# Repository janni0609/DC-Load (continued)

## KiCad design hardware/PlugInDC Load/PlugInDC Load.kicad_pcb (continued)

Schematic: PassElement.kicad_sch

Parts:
C1: 100n; C_0603_1608Metric; not fitted
C2: 10n; C_0603_1608Metric
C3: 100n; C_0603_1608Metric
D1, D2: 1N4148WX; D_SOD-323
F1: 10A; Fuse_1206_3216Metric
H1, H2: M3; MountingHole_3.2mm_M3_DIN965_Pad
Q1: MJH6284; MR30
R2, R3, R4, R10, R11: 1k; R_0603_1608Metric
R5: 500; R_0603_1608Metric; not fitted
R6: 10k; R_0603_1608Metric
R7, R9: 62k; R_0603_1608Metric
R8: 150; R_1206_3216Metric
R12: 0,005; R_2512_6332Metric
TP1: Int-; TestPoint_Pad_D1.0mm
TP2: CurrO; TestPoint_Pad_D1.0mm
TP3: IntO; TestPoint_Pad_D1.0mm
TP4: B; TestPoint_Pad_D1.0mm
TP5: CrrH; TestPoint_Pad_D1.0mm
TP6: CurrL; TestPoint_Pad_D1.0mm
U3: TLV9152; SOT-23-8

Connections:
+5V: C3.2, U3.8 (V+); also elsewhere on the board
/PassElementsAll/Imeas: R4.1; also elsewhere on the board
/PassElementsAll/Iset: R2.1; also elsewhere on the board
/PassElementsAll/ON/OFF: D2.1 (K); also elsewhere on the board
/PassElementsAll/PassElement2/Emitter: F1.1, Q1.3 (E)
/PassElementsAll/PassElement2/R_to_F: F1.2, R10.2, R12.1, TP5.1 (1_1)
/PassElementsAll/unreg_mon: D1.1 (K); also elsewhere on the board
GND: C3.1, R6.1, R9.2, U3.4 (V-); also elsewhere on the board
GNDPWR: H1.1 (1_1), R11.2, R12.2, TP6.1 (1_1); also elsewhere on the board
unnamed: C1.2, R5.1
unnamed: C2.2, D1.2 (A), R5.2, R6.2, R8.1, TP3.1 (1_1), U3.1
unnamed: D2.2 (A), Q1.1 (B), R8.2, TP4.1 (1_1)
unnamed: R3.2, R4.2, R7.1, TP2.1 (1_1), U3.7
unnamed: R2.2, U3.3 (+)
unnamed: C1.1, C2.1, R3.1, TP1.1 (1_1), U3.2 (-)
unnamed: R9.1, R10.1, U3.5 (+)
unnamed: R7.2, R11.1, U3.6 (-)
VBUS: H2.1 (1_1), Q1.2 (C); also elsewhere on the board

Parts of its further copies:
C23, C26, C29, C32, C35, C38, C41, C44, C47, C50, C53, C56, C59: 100n; C_0603_1608Metric; not fitted
C24, C27, C30, C33, C36, C39, C42, C45, C48, C51, C54, C57, C60: 10n; C_0603_1608Metric
C25, C28, C31, C34, C37, C40, C43, C46, C49, C52, C55, C58, C61: 100n; C_0603_1608Metric
D15, D16, D17, D18, D19, D20, D21, D22, D23, D24, D25, D26, D27, D28, D29, D30, D31, D32, D33, D34, D35, D36, D37, D38, D39, D40: 1N4148WX; D_SOD-323
F4, F5, F6, F7, F8, F9, F10, F11, F12, F13, F14, F15, F16: 10A; Fuse_1206_3216Metric
H5, H6, H7, H8, H9, H10, H11, H12, H13, H14, H15, H16, H17, H18, H19, H20, H21, H22, H23, H24, H25, H26, H27, H28, H29, H30: M3; MountingHole_3.2mm_M3_DIN965_Pad
Q3, Q4, Q5, Q6, Q7, Q8, Q9, Q10, Q11, Q12, Q13, Q14, Q15: MJH6284; MR30
R23, R24, R25, R31, R32, R34, R35, R36, R42, R43, R45, R46, R47, R53, R54, R56, R57, R58, R64, R65, R67, R68, R69, R75, R76, R78, R79, R80, R86, R87, R89, R90, R91, R97, R98, R100, R101, R102, R108, R109, R111, R112, R113, R119, R120, R122, R123, R124, R130, R131, R133, R134, R135, R141, R142, R144, R145, R146, R152, R153, R155, R156, R157, R163, R164: 1k; R_0603_1608Metric
R26, R37, R48, R59, R70, R81, R92, R103, R114, R125, R136, R147, R158: 500; R_0603_1608Metric; not fitted
R27, R38, R49, R60, R71, R82, R93, R104, R115, R126, R137, R148, R159: 10k; R_0603_1608Metric
R28, R30, R39, R41, R50, R52, R61, R63, R72, R74, R83, R85, R94, R96, R105, R107, R116, R118, R127, R129, R138, R140, R149, R151, R160, R162: 62k; R_0603_1608Metric
R29, R40, R51, R62, R73, R84, R95, R106, R117, R128, R139, R150, R161: 150; R_1206_3216Metric
R33, R44, R55, R66, R77, R88, R99, R110, R121, R132, R143, R154, R165: 0,005; R_2512_6332Metric
TP7, TP13, TP19, TP25, TP31, TP37, TP43, TP49, TP55, TP61, TP67, TP73, TP79: Int-; TestPoint_Pad_D1.0mm
TP8, TP14, TP20, TP26, TP32, TP38, TP44, TP50, TP56, TP62, TP68, TP74, TP80: CurrO; TestPoint_Pad_D1.0mm
TP9, TP15, TP21, TP27, TP33, TP39, TP45, TP51, TP57, TP63, TP69, TP75, TP81: IntO; TestPoint_Pad_D1.0mm
TP10, TP16, TP22, TP28, TP34, TP40, TP46, TP52, TP58, TP64, TP70, TP76, TP82: B; TestPoint_Pad_D1.0mm
TP11, TP17, TP23, TP29, TP35, TP41, TP47, TP53, TP59, TP65, TP71, TP77, TP83: CrrH; TestPoint_Pad_D1.0mm
TP12, TP18, TP24, TP30, TP36, TP42, TP48, TP54, TP60, TP66, TP72, TP78, TP84: CurrL; TestPoint_Pad_D1.0mm
U8, U9, U10, U11, U12, U13, U14, U15, U16, U17, U18, U19, U20: TLV9152; SOT-23-8

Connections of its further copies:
+5V: C25.2, C28.2, C31.2, C34.2, C37.2, C40.2, C43.2, C46.2, C49.2, C52.2, C55.2, C58.2, C61.2, U8.8 (V+), U9.8 (V+), U10.8 (V+), U11.8 (V+), U12.8 (V+), U13.8 (V+), U14.8 (V+), U15.8 (V+), U16.8 (V+), U17.8 (V+), U18.8 (V+), U19.8 (V+), U20.8 (V+); also elsewhere on the board
/PassElementsAll/Imeas: R25.1, R36.1, R47.1, R58.1, R69.1, R80.1, R91.1, R102.1, R113.1, R124.1, R135.1, R146.1, R157.1; also elsewhere on the board
/PassElementsAll/Iset: R23.1, R34.1, R45.1, R56.1, R67.1, R78.1, R89.1, R100.1, R111.1, R122.1, R133.1, R144.1, R155.1; also elsewhere on the board
/PassElementsAll/ON/OFF: D16.1 (K), D18.1 (K), D20.1 (K), D22.1 (K), D24.1 (K), D26.1 (K), D28.1 (K), D30.1 (K), D32.1 (K), D34.1 (K), D36.1 (K), D38.1 (K), D40.1 (K); also elsewhere on the board
/PassElementsAll/PassElement1/Emitter: F4.1, Q3.3 (E)
/PassElementsAll/PassElement1/R_to_F: F4.2, R31.2, R33.1, TP11.1 (1_1)
/PassElementsAll/PassElement3/Emitter: F5.1, Q4.3 (E)
/PassElementsAll/PassElement3/R_to_F: F5.2, R42.2, R44.1, TP17.1 (1_1)
/PassElementsAll/PassElement4/Emitter: F6.1, Q5.3 (E)
/PassElementsAll/PassElement4/R_to_F: F6.2, R53.2, R55.1, TP23.1 (1_1)
/PassElementsAll/PassElement5/Emitter: F7.1, Q6.3 (E)
/PassElementsAll/PassElement5/R_to_F: F7.2, R64.2, R66.1, TP29.1 (1_1)
/PassElementsAll/PassElement6/Emitter: F8.1, Q7.3 (E)
/PassElementsAll/PassElement6/R_to_F: F8.2, R75.2, R77.1, TP35.1 (1_1)
/PassElementsAll/PassElement7/Emitter: F9.1, Q8.3 (E)
/PassElementsAll/PassElement7/R_to_F: F9.2, R86.2, R88.1, TP41.1 (1_1)
/PassElementsAll/PassElement8/Emitter: F10.1, Q9.3 (E)
/PassElementsAll/PassElement8/R_to_F: F10.2, R97.2, R99.1, TP47.1 (1_1)
/PassElementsAll/PassElement9/Emitter: F11.1, Q10.3 (E)
/PassElementsAll/PassElement9/R_to_F: F11.2, R108.2, R110.1, TP53.1 (1_1)
/PassElementsAll/PassElement10/Emitter: F12.1, Q11.3 (E)
/PassElementsAll/PassElement10/R_to_F: F12.2, R119.2, R121.1, TP59.1 (1_1)
/PassElementsAll/PassElement11/Emitter: F13.1, Q12.3 (E)
/PassElementsAll/PassElement11/R_to_F: F13.2, R130.2, R132.1, TP65.1 (1_1)
/PassElementsAll/PassElement12/Emitter: F14.1, Q13.3 (E)
/PassElementsAll/PassElement12/R_to_F: F14.2, R141.2, R143.1, TP71.1 (1_1)
/PassElementsAll/PassElement13/Emitter: F16.1, Q15.3 (E)
/PassElementsAll/PassElement13/R_to_F: F16.2, R163.2, R165.1, TP83.1 (1_1)
/PassElementsAll/PassElement14/Emitter: F15.1, Q14.3 (E)
/PassElementsAll/PassElement14/R_to_F: F15.2, R152.2, R154.1, TP77.1 (1_1)
/PassElementsAll/unreg_mon: D15.1 (K), D17.1 (K), D19.1 (K), D21.1 (K), D23.1 (K), D25.1 (K), D27.1 (K), D29.1 (K), D31.1 (K), D33.1 (K), D35.1 (K), D37.1 (K), D39.1 (K); also elsewhere on the board
GND: C25.1, C28.1, C31.1, C34.1, C37.1, C40.1, C43.1, C46.1, C49.1, C52.1, C55.1, C58.1, C61.1, R27.1, R30.2, R38.1, R41.2, R49.1, R52.2, R60.1, R63.2, R71.1, R74.2, R82.1, R85.2, R93.1, R96.2, R104.1, R107.2, R115.1, R118.2, R126.1, R129.2, R137.1, R140.2, R148.1, R151.2, R159.1, R162.2, U8.4 (V-), U9.4 (V-), U10.4 (V-), U11.4 (V-), U12.4 (V-), U13.4 (V-), U14.4 (V-), U15.4 (V-), U16.4 (V-), U17.4 (V-), U18.4 (V-), U19.4 (V-), U20.4 (V-); also elsewhere on the board
GNDPWR: H5.1 (1_1), H7.1 (1_1), H9.1 (1_1), H11.1 (1_1), H13.1 (1_1), H15.1 (1_1), H17.1 (1_1), H19.1 (1_1), H21.1 (1_1), H23.1 (1_1), H25.1 (1_1), H27.1 (1_1), H29.1 (1_1), R32.2, R33.2, R43.2, R44.2, R54.2, R55.2, R65.2, R66.2, R76.2, R77.2, R87.2, R88.2, R98.2, R99.2, R109.2, R110.2, R120.2, R121.2, R131.2, R132.2, R142.2, R143.2, R153.2, R154.2, R164.2, R165.2, TP12.1 (1_1), TP18.1 (1_1), TP24.1 (1_1), TP30.1 (1_1), TP36.1 (1_1), TP42.1 (1_1), TP48.1 (1_1), TP54.1 (1_1), TP60.1 (1_1), TP66.1 (1_1), TP72.1 (1_1), TP78.1 (1_1), TP84.1 (1_1); also elsewhere on the board
unnamed: C23.2, R26.1
unnamed: C26.2, R37.1
unnamed: C29.2, R48.1
unnamed: C32.2, R59.1
unnamed: C35.2, R70.1
unnamed: C38.2, R81.1
unnamed: C41.2, R92.1
unnamed: C44.2, R103.1
unnamed: C47.2, R114.1
unnamed: C50.2, R125.1
unnamed: C53.2, R136.1
unnamed: C56.2, R147.1
unnamed: C59.2, R158.1
unnamed: C24.2, D15.2 (A), R26.2, R27.2, R29.1, TP9.1 (1_1), U8.1
unnamed: D16.2 (A), Q3.1 (B), R29.2, TP10.1 (1_1)
unnamed: C27.2, D17.2 (A), R37.2, R38.2, R40.1, TP15.1 (1_1), U9.1
unnamed: D18.2 (A), Q4.1 (B), R40.2, TP16.1 (1_1)
unnamed: C30.2, D19.2 (A), R48.2, R49.2, R51.1, TP21.1 (1_1), U10.1
unnamed: D20.2 (A), Q5.1 (B), R51.2, TP22.1 (1_1)
unnamed: C33.2, D21.2 (A), R59.2, R60.2, R62.1, TP27.1 (1_1), U11.1
unnamed: D22.2 (A), Q6.1 (B), R62.2, TP28.1 (1_1)
unnamed: C36.2, D23.2 (A), R70.2, R71.2, R73.1, TP33.1 (1_1), U12.1
unnamed: D24.2 (A), Q7.1 (B), R73.2, TP34.1 (1_1)
unnamed: C39.2, D25.2 (A), R81.2, R82.2, R84.1, TP39.1 (1_1), U13.1
unnamed: D26.2 (A), Q8.1 (B), R84.2, TP40.1 (1_1)
unnamed: C42.2, D27.2 (A), R92.2, R93.2, R95.1, TP45.1 (1_1), U14.1
unnamed: D28.2 (A), Q9.1 (B), R95.2, TP46.1 (1_1)
unnamed: C45.2, D29.2 (A), R103.2, R104.2, R106.1, TP51.1 (1_1), U15.1
unnamed: D30.2 (A), Q10.1 (B), R106.2, TP52.1 (1_1)
unnamed: C48.2, D31.2 (A), R114.2, R115.2, R117.1, TP57.1 (1_1), U16.1
unnamed: D32.2 (A), Q11.1 (B), R117.2, TP58.1 (1_1)
unnamed: C51.2, D33.2 (A), R125.2, R126.2, R128.1, TP63.1 (1_1), U17.1
unnamed: D34.2 (A), Q12.1 (B), R128.2, TP64.1 (1_1)
unnamed: C54.2, D35.2 (A), R136.2, R137.2, R139.1, TP69.1 (1_1), U18.1
unnamed: D36.2 (A), Q13.1 (B), R139.2, TP70.1 (1_1)
unnamed: C57.2, D37.2 (A), R147.2, R148.2, R150.1, TP75.1 (1_1), U19.1
unnamed: D38.2 (A), Q14.1 (B), R150.2, TP76.1 (1_1)
unnamed: C60.2, D39.2 (A), R158.2, R159.2, R161.1, TP81.1 (1_1), U20.1
unnamed: D40.2 (A), Q15.1 (B), R161.2, TP82.1 (1_1)
unnamed: R24.2, R25.2, R28.1, TP8.1 (1_1), U8.7
unnamed: R35.2, R36.2, R39.1, TP14.1 (1_1), U9.7
unnamed: R46.2, R47.2, R50.1, TP20.1 (1_1), U10.7
unnamed: R57.2, R58.2, R61.1, TP26.1 (1_1), U11.7
unnamed: R68.2, R69.2, R72.1, TP32.1 (1_1), U12.7
unnamed: R79.2, R80.2, R83.1, TP38.1 (1_1), U13.7
unnamed: R90.2, R91.2, R94.1, TP44.1 (1_1), U14.7
unnamed: R101.2, R102.2, R105.1, TP50.1 (1_1), U15.7
unnamed: R112.2, R113.2, R116.1, TP56.1 (1_1), U16.7
unnamed: R123.2, R124.2, R127.1, TP62.1 (1_1), U17.7
unnamed: R134.2, R135.2, R138.1, TP68.1 (1_1), U18.7
unnamed: R145.2, R146.2, R149.1, TP74.1 (1_1), U19.7
unnamed: R156.2, R157.2, R160.1, TP80.1 (1_1), U20.7
unnamed: R23.2, U8.3 (+)
unnamed: C23.1, C24.1, R24.1, TP7.1 (1_1), U8.2 (-)
unnamed: R30.1, R31.1, U8.5 (+)
unnamed: R28.2, R32.1, U8.6 (-)
unnamed: R34.2, U9.3 (+)
unnamed: C26.1, C27.1, R35.1, TP13.1 (1_1), U9.2 (-)
unnamed: R41.1, R42.1, U9.5 (+)
unnamed: R39.2, R43.1, U9.6 (-)
unnamed: R45.2, U10.3 (+)
unnamed: C29.1, C30.1, R46.1, TP19.1 (1_1), U10.2 (-)
unnamed: R52.1, R53.1, U10.5 (+)
unnamed: R50.2, R54.1, U10.6 (-)
unnamed: R56.2, U11.3 (+)
unnamed: C32.1, C33.1, R57.1, TP25.1 (1_1), U11.2 (-)
unnamed: R63.1, R64.1, U11.5 (+)
unnamed: R61.2, R65.1, U11.6 (-)
unnamed: R67.2, U12.3 (+)
unnamed: C35.1, C36.1, R68.1, TP31.1 (1_1), U12.2 (-)
unnamed: R74.1, R75.1, U12.5 (+)
unnamed: R72.2, R76.1, U12.6 (-)
unnamed: R78.2, U13.3 (+)
unnamed: C38.1, C39.1, R79.1, TP37.1 (1_1), U13.2 (-)
unnamed: R85.1, R86.1, U13.5 (+)
unnamed: R83.2, R87.1, U13.6 (-)
unnamed: R89.2, U14.3 (+)
unnamed: C41.1, C42.1, R90.1, TP43.1 (1_1), U14.2 (-)
unnamed: R96.1, R97.1, U14.5 (+)
unnamed: R94.2, R98.1, U14.6 (-)
unnamed: R100.2, U15.3 (+)
unnamed: C44.1, C45.1, R101.1, TP49.1 (1_1), U15.2 (-)
unnamed: R107.1, R108.1, U15.5 (+)
unnamed: R105.2, R109.1, U15.6 (-)
unnamed: R111.2, U16.3 (+)
unnamed: C47.1, C48.1, R112.1, TP55.1 (1_1), U16.2 (-)
unnamed: R118.1, R119.1, U16.5 (+)
unnamed: R116.2, R120.1, U16.6 (-)
unnamed: R122.2, U17.3 (+)
unnamed: C50.1, C51.1, R123.1, TP61.1 (1_1), U17.2 (-)
unnamed: R129.1, R130.1, U17.5 (+)
unnamed: R127.2, R131.1, U17.6 (-)
unnamed: R133.2, U18.3 (+)
unnamed: C53.1, C54.1, R134.1, TP67.1 (1_1), U18.2 (-)
unnamed: R140.1, R141.1, U18.5 (+)
unnamed: R138.2, R142.1, U18.6 (-)
unnamed: R144.2, U19.3 (+)
unnamed: C56.1, C57.1, R145.1, TP73.1 (1_1), U19.2 (-)
unnamed: R151.1, R152.1, U19.5 (+)
unnamed: R149.2, R153.1, U19.6 (-)
unnamed: R155.2, U20.3 (+)
unnamed: C59.1, C60.1, R156.1, TP79.1 (1_1), U20.2 (-)
unnamed: R162.1, R163.1, U20.5 (+)
unnamed: R160.2, R164.1, U20.6 (-)
VBUS: H6.1 (1_1), H8.1 (1_1), H10.1 (1_1), H12.1 (1_1), H14.1 (1_1), H16.1 (1_1), H18.1 (1_1), H20.1 (1_1), H22.1 (1_1), H24.1 (1_1), H26.1 (1_1), H28.1 (1_1), H30.1 (1_1), Q3.2 (C), Q4.2 (C), Q5.2 (C), Q6.2 (C), Q7.2 (C), Q8.2 (C), Q9.2 (C), Q10.2 (C), Q11.2 (C), Q12.2 (C), Q13.2 (C), Q14.2 (C), Q15.2 (C); also elsewhere on the board

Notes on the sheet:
Supply: max 5V ~25mA
0 - 2,5V 0 - 8,0645A
2,5V
G = 62

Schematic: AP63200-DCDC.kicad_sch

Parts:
C14: 10u; C_1206_3216Metric
C15, C16, C22: 100n; C_0603_1608Metric
C17: 100p; C_0603_1608Metric
C18, C19, C20, C21: 10u; C_0805_2012Metric
L1: 10u; L_APV_ANR8040
R21: 150k; R_0603_1608Metric
R22: 20k; R_0603_1608Metric
U7: AP63200WU; TSOT-23-6

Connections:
+12V: C14.1, C15.1, U7.2 (EN), U7.3 (IN); also elsewhere on the board
/Power Supply/AP63200-DCDC/SW: C16.2, L1.1, U7.5 (SW)
/Power Supply/AP63200-DCDC/Vout: C17.1, C18.1, C19.1, C20.1, C21.1, C22.1, L1.2, R21.1; also elsewhere on the board
GND: C14.2, C15.2, C18.2, C19.2, C20.2, C21.2, C22.2, R22.2, U7.4 (GND); also elsewhere on the board
unnamed: C16.1, U7.6 (BST)
unnamed: C17.2, R21.2, R22.1, U7.1 (FB)

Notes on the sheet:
6,8V

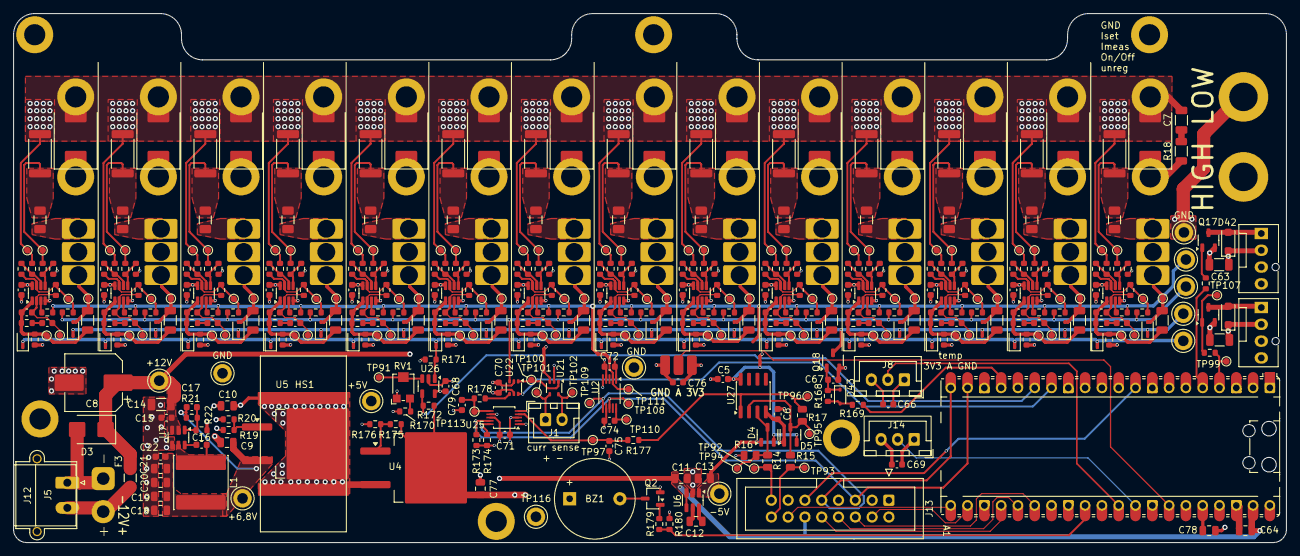
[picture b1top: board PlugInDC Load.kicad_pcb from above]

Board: 4 copper layers, 192.5 x 80.0 mm, 525 parts (0 on the bottom side), 201 nets.

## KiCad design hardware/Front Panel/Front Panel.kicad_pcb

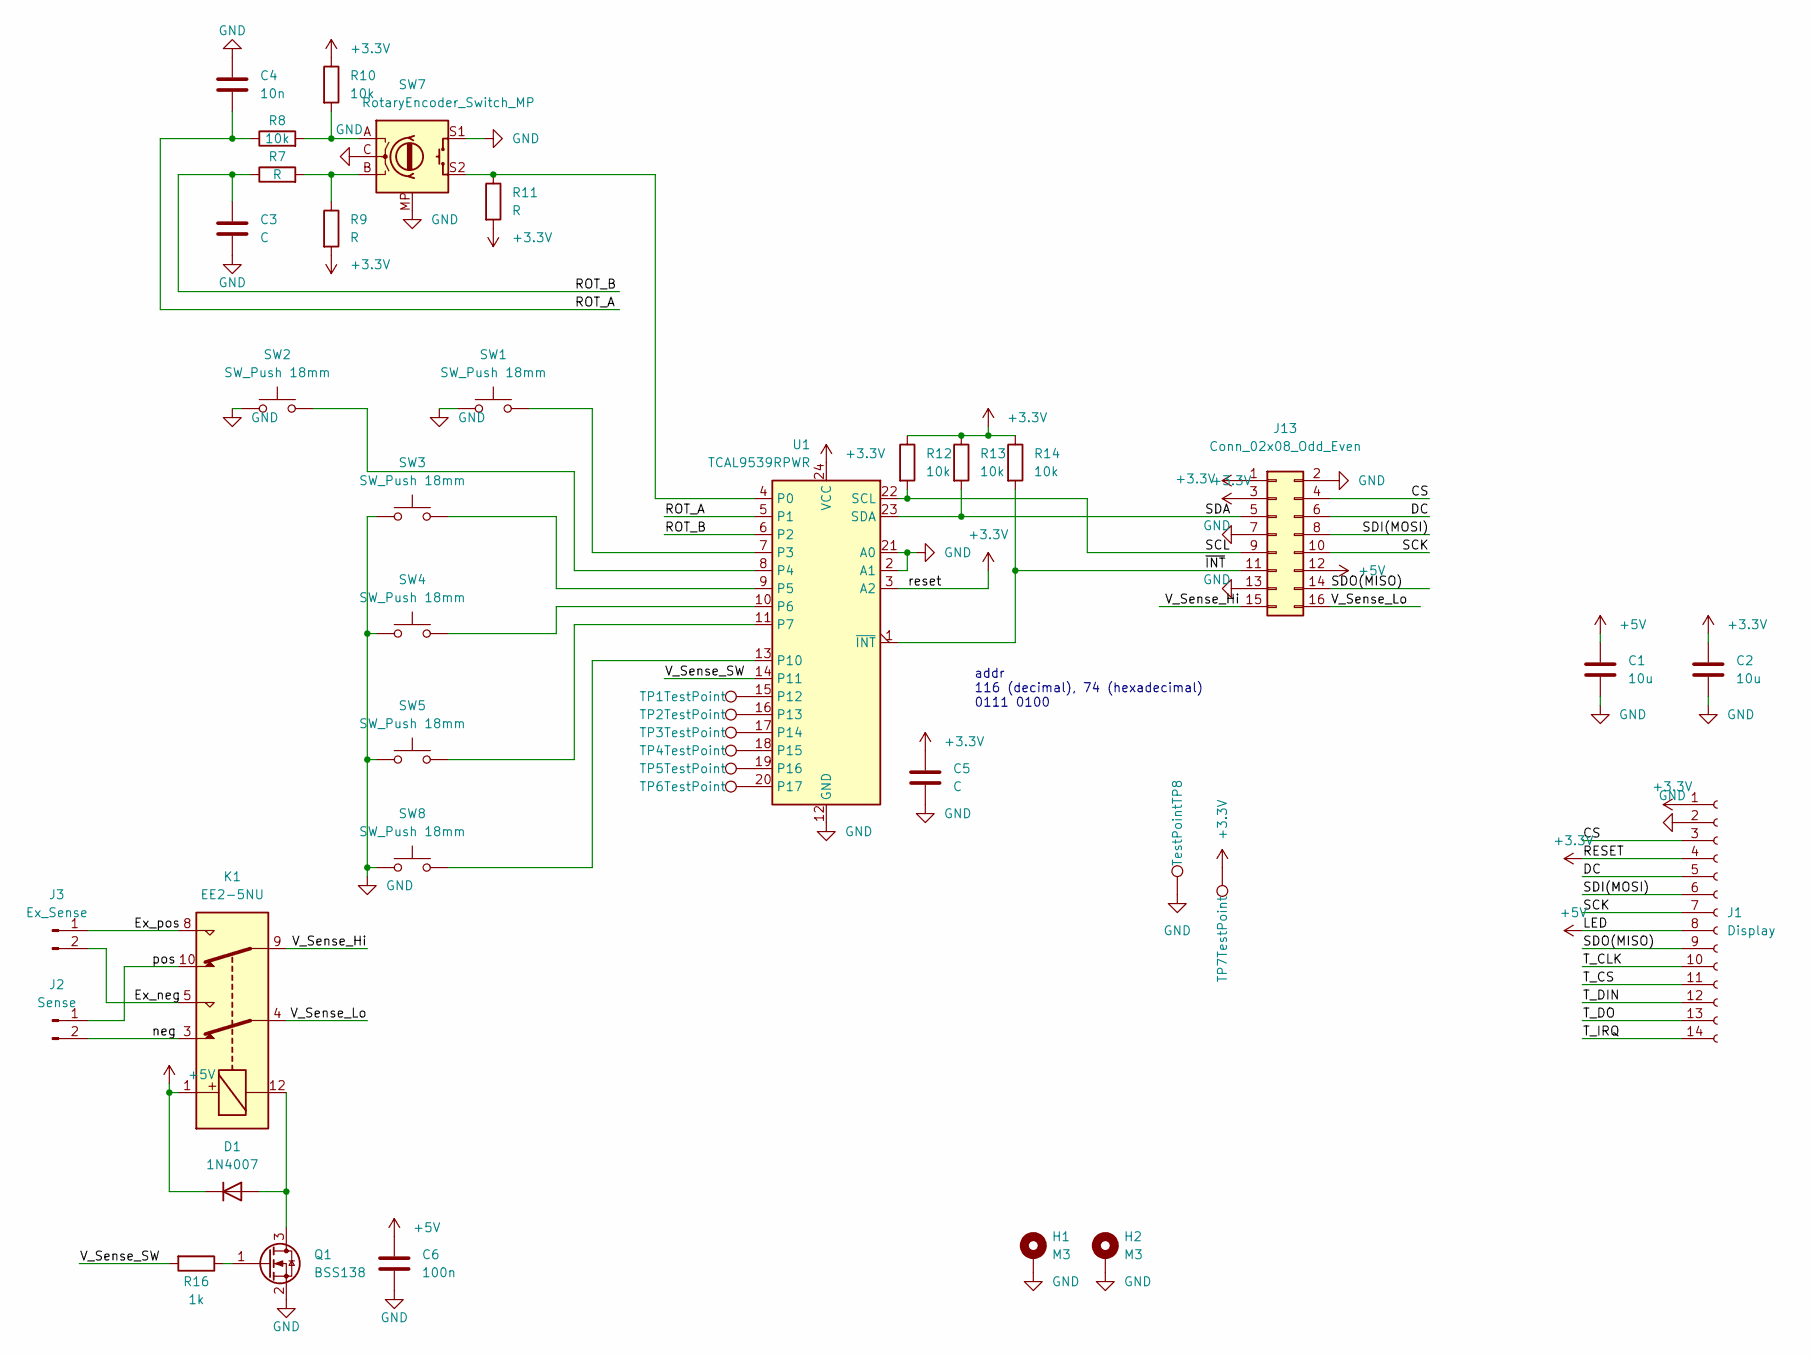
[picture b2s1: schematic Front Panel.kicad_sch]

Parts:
C1, C2: 10u
C3, C5: C
C4: 10n
C6: 100n
D1: 1N4007; D_SOD-123F
H1, H2: M3
J1: Display
J2: Sense
J3: Ex_Sense
J13: Conn_02x08_Odd_Even
K1: EE2-5NU; Relay_DPDT_Kemet_EE2_NU
Q1: BSS138; SOT-23
R7, R9, R11: R
R8, R10, R12, R13, R14: 10k
R16: 1k
SW1, SW2, SW3, SW4, SW5, SW8: SW_Push 18mm
SW7: RotaryEncoder_Switch_MP
TP1, TP2, TP3, TP4, TP5, TP6: TestPoint; TestPoint_Pad_D1.0mm
TP7, TP8: TestPoint; TestPoint_Pad_D1.5mm
U1: TCAL9539RPWR; TSSOP-24_4.4x7.8mm_P0.65mm

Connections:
+3.3V: C2.1, C5.1, J1.1, J1.4, J13.1, J13.3, R9.2, R10.1, R11.2, R12.1, R13.1, R14.1, TP7.1 (1_1), U1.3 (A2), U1.24 (VCC)
+5V: C1.1, C6.1, D1.1 (K), J1.8, J13.12, K1.1
/CS: J1.3, J13.4
/DC: J1.5, J13.6
/Ex_neg: J3.2, K1.5
/Ex_pos: J3.1, K1.8
/ROT_A: C4.1, R8.1, U1.5 (P1)
/ROT_B: C3.1, R7.1, U1.6 (P2)
/SCK: J1.7, J13.10
/SCL: J13.9, R12.2, U1.22 (SCL)
/SDA: J13.5, R13.2, U1.23 (SDA)
/SDI(MOSI): J1.6, J13.8
/SDO(MISO): J1.9, J13.14
/T_CLK: J1.10
/T_CS: J1.11
/T_DIN: J1.12
/T_DO: J1.13
/T_IRQ: J1.14
/V_Sense_Hi: J13.15, K1.9
/V_Sense_Lo: J13.16, K1.4
/V_Sense_SW: R16.2, U1.14 (P11)
/neg: J2.2, K1.3
/pos: J2.1, K1.10
/~INT: J13.11, R14.2, U1.1 (~INT)
GND: C1.2, C2.2, C3.2, C4.2, C5.2, C6.2, H1.1 (1_1), H2.1 (1_1), J1.2, J13.2, J13.7, J13.13, Q1.2 (S), SW1.1, SW2.1, SW3.1, SW4.1, SW5.1, SW7.C, SW7.MP, SW7.S1, SW8.1, TP8.1 (1_1), U1.2 (A1), U1.12 (GND), U1.21 (A0)
unnamed: D1.2 (A), K1.12, Q1.3 (D)
unnamed: Q1.1 (G), R16.1
unnamed: R7.2, R9.1, SW7.B
unnamed: R8.2, R10.2, SW7.A
unnamed: R11.1, SW7.S2, U1.4 (P0)
unnamed: SW1.2, U1.7 (P3)
unnamed: SW2.2, U1.8 (P4)
unnamed: SW3.2, U1.9 (P5)
unnamed: SW4.2, U1.10 (P6)
unnamed: SW5.2, U1.11 (P7)
unnamed: SW8.2, U1.13 (P10)
unnamed: TP1.1 (1_1), U1.15 (P12)
unnamed: TP2.1 (1_1), U1.16 (P13)
unnamed: TP3.1 (1_1), U1.17 (P14)
unnamed: TP4.1 (1_1), U1.18 (P15)
unnamed: TP5.1 (1_1), U1.19 (P16)
unnamed: TP6.1 (1_1), U1.20 (P17)

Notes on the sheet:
addr 116 (decimal), 74 (hexadecimal) 0111 0100

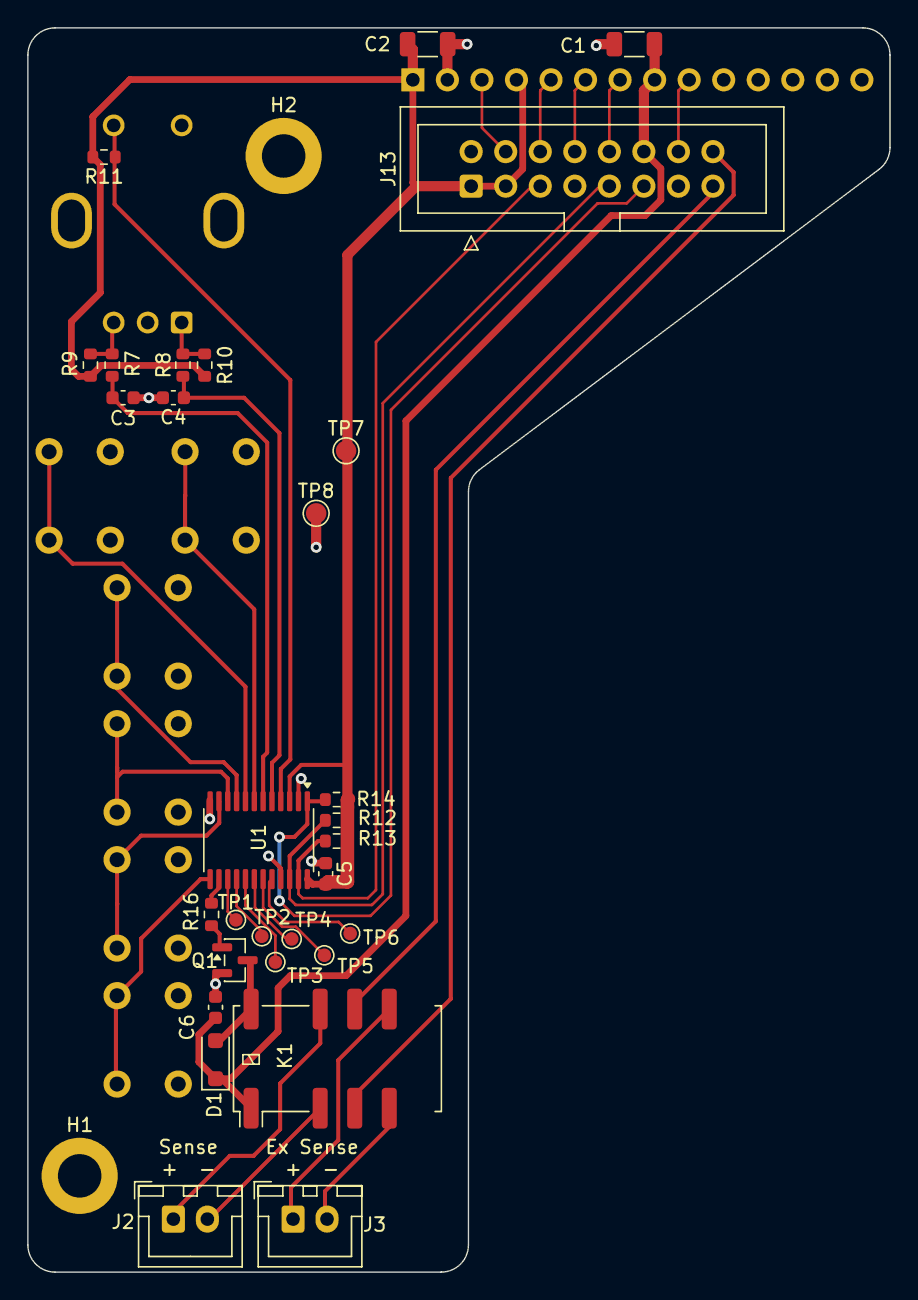
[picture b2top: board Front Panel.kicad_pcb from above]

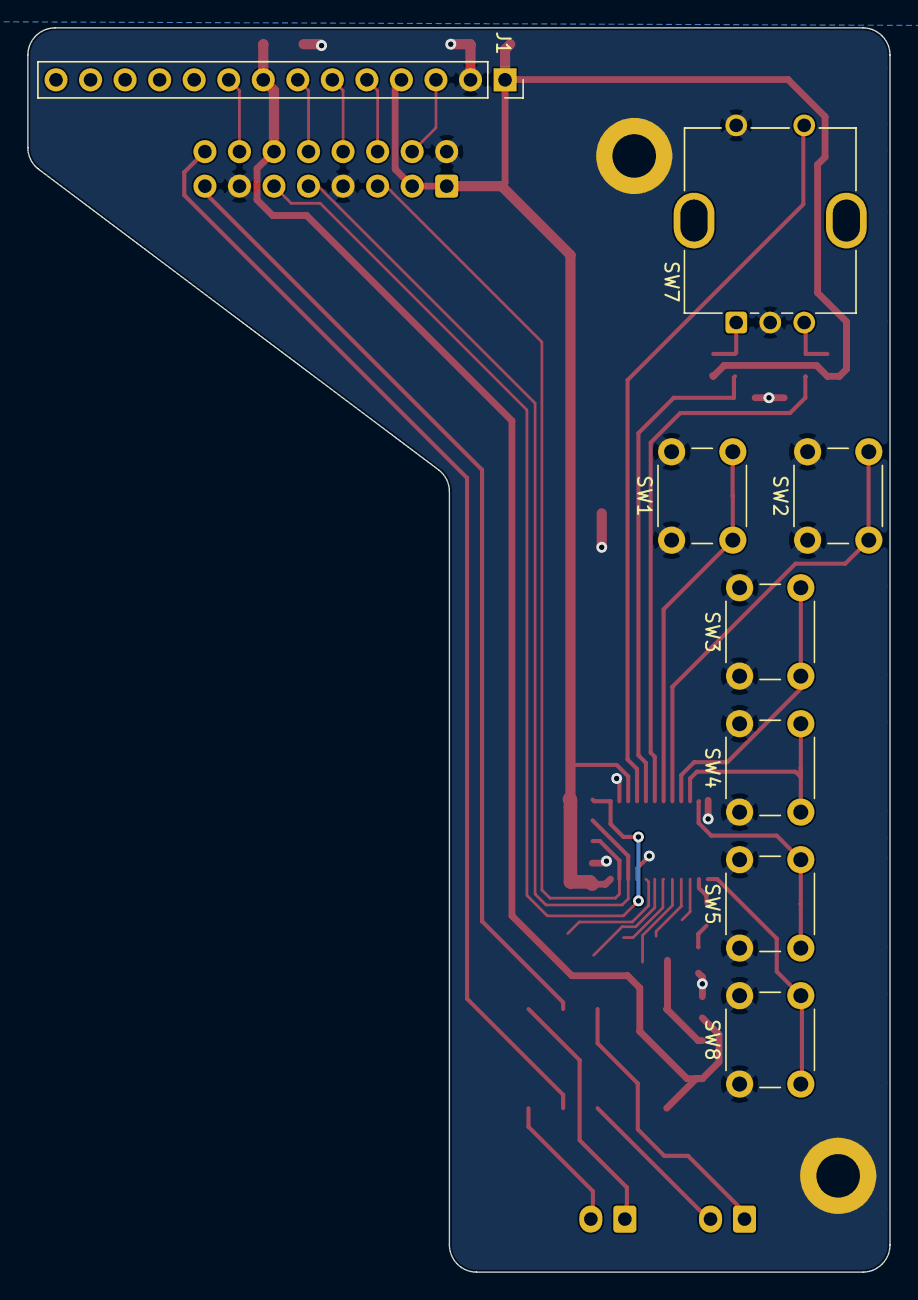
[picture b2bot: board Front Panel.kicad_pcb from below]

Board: 2 copper layers, 63.4 x 91.5 mm, 40 parts (8 on the bottom side), 37 nets.

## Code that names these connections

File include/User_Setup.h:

// User setup for TFT_eSPI library - Raspberry Pi Pico with SPI display

#ifndef USER_SETUP_H_INCLUDED
#define USER_SETUP_H_INCLUDED

// ===========================
// Display Model Configuration
// ===========================
// Uncomment your display model:
//#define ILI9341_DRIVER       // 2.4" ILI9341 SPI display
 #define ILI9488_DRIVER    // 3.5" ILI9488 SPI display  
// #define ST7735_DRIVER     // 1.8" ST7735 SPI display
// #define ST7789_DRIVER     // 1.3" ST7789 SPI display

// ===========================
// SPI Pin Configuration for Raspberry Pi Pico
// ===========================
#define TFT_MOSI 19    // GPIO19
#define TFT_MISO 16    // GPIO16
#define TFT_SCLK 18    // GPIO18
#define TFT_CS   17    // GPIO17 (Chip Select)
#define TFT_DC   20    // GPIO20 (Data/Command)
#define TFT_RST  -1    // Set to -1 if RST is connected to 3.3V

// Optional: backlight pin (set to -1 if not using)
#define TFT_BL   -1    // Backlight control pin

// ===========================
// SPI Speed
// ===========================
#define SPI_FREQUENCY  75000000    // 75 MHz - RP2350 max (sys_clk 150 MHz / 2)

// ===========================
// Display Orientation and Size
// ===========================
#define TFT_WIDTH  240   // confirmed by hardware
#define TFT_HEIGHT 320   // confirmed by hardware
// ===========================
// Font Smoothing
// ===========================
#define SMOOTH_FONT

// ===========================
// Color Order
// ===========================
// ILI9488 panels sometimes ship with BGR order instead of RGB.
// If blue appears as red (or vice versa), swap this define.
#define TFT_RGB_ORDER TFT_RGB
#define TFT_INVERSION_ON   // try TFT_RGB if colors are still wrong


// ===========================
// Library Options
// ===========================
#define SUPPORT_TRANSACTIONS

#endif // USER_SETUP_H_INCLUDED

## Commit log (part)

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2026-05-11 add data to repo
2026-05-11 update cocation
2026-05-11 add pdf and .claude
2026-05-15 added OTP and calibration
2026-05-15 lower startup time
2026-05-15 added button debounce and more cal points for volatage
2026-05-31 correkt target
